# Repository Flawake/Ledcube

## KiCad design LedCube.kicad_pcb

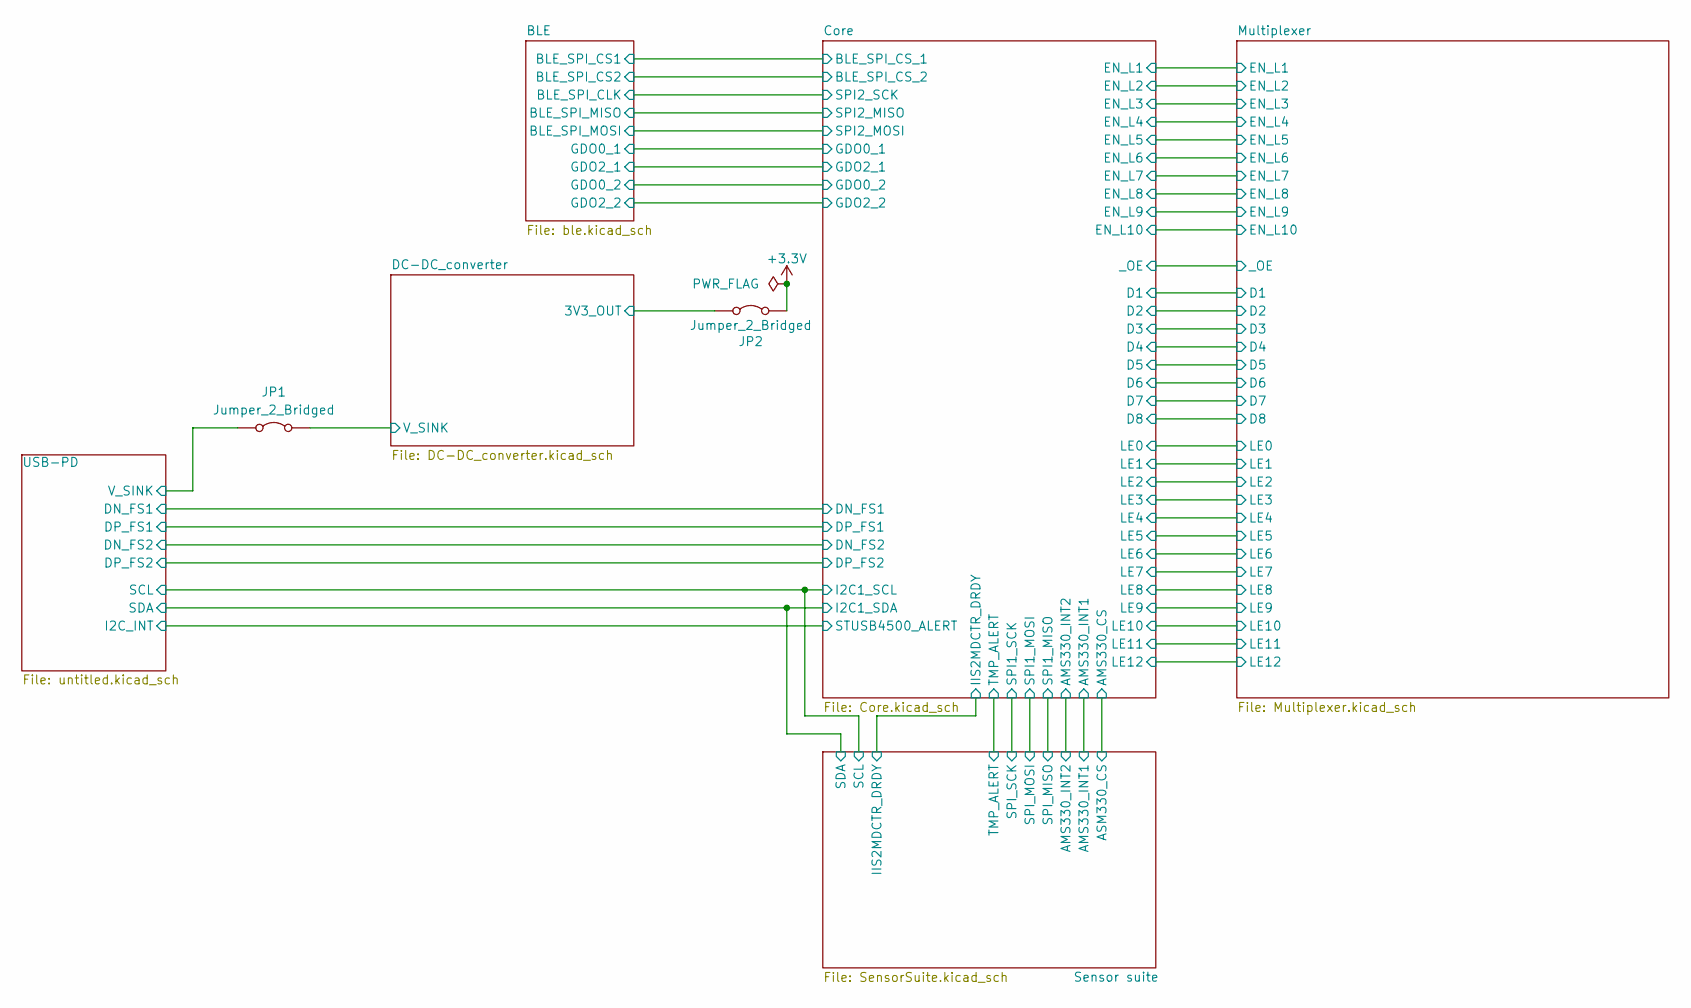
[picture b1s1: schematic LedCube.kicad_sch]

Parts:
JP1, JP2: Jumper_2_Bridged; R_0805_2012Metric

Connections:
+3.3V: JP2.2 (B); also elsewhere on the board
/DC-DC_converter/3V3_OUT: JP2.1 (A); also elsewhere on the board
/DC-DC_converter/V_SINK: JP1.2 (B); also elsewhere on the board
/USB-PD/V_SINK: JP1.1 (A); also elsewhere on the board

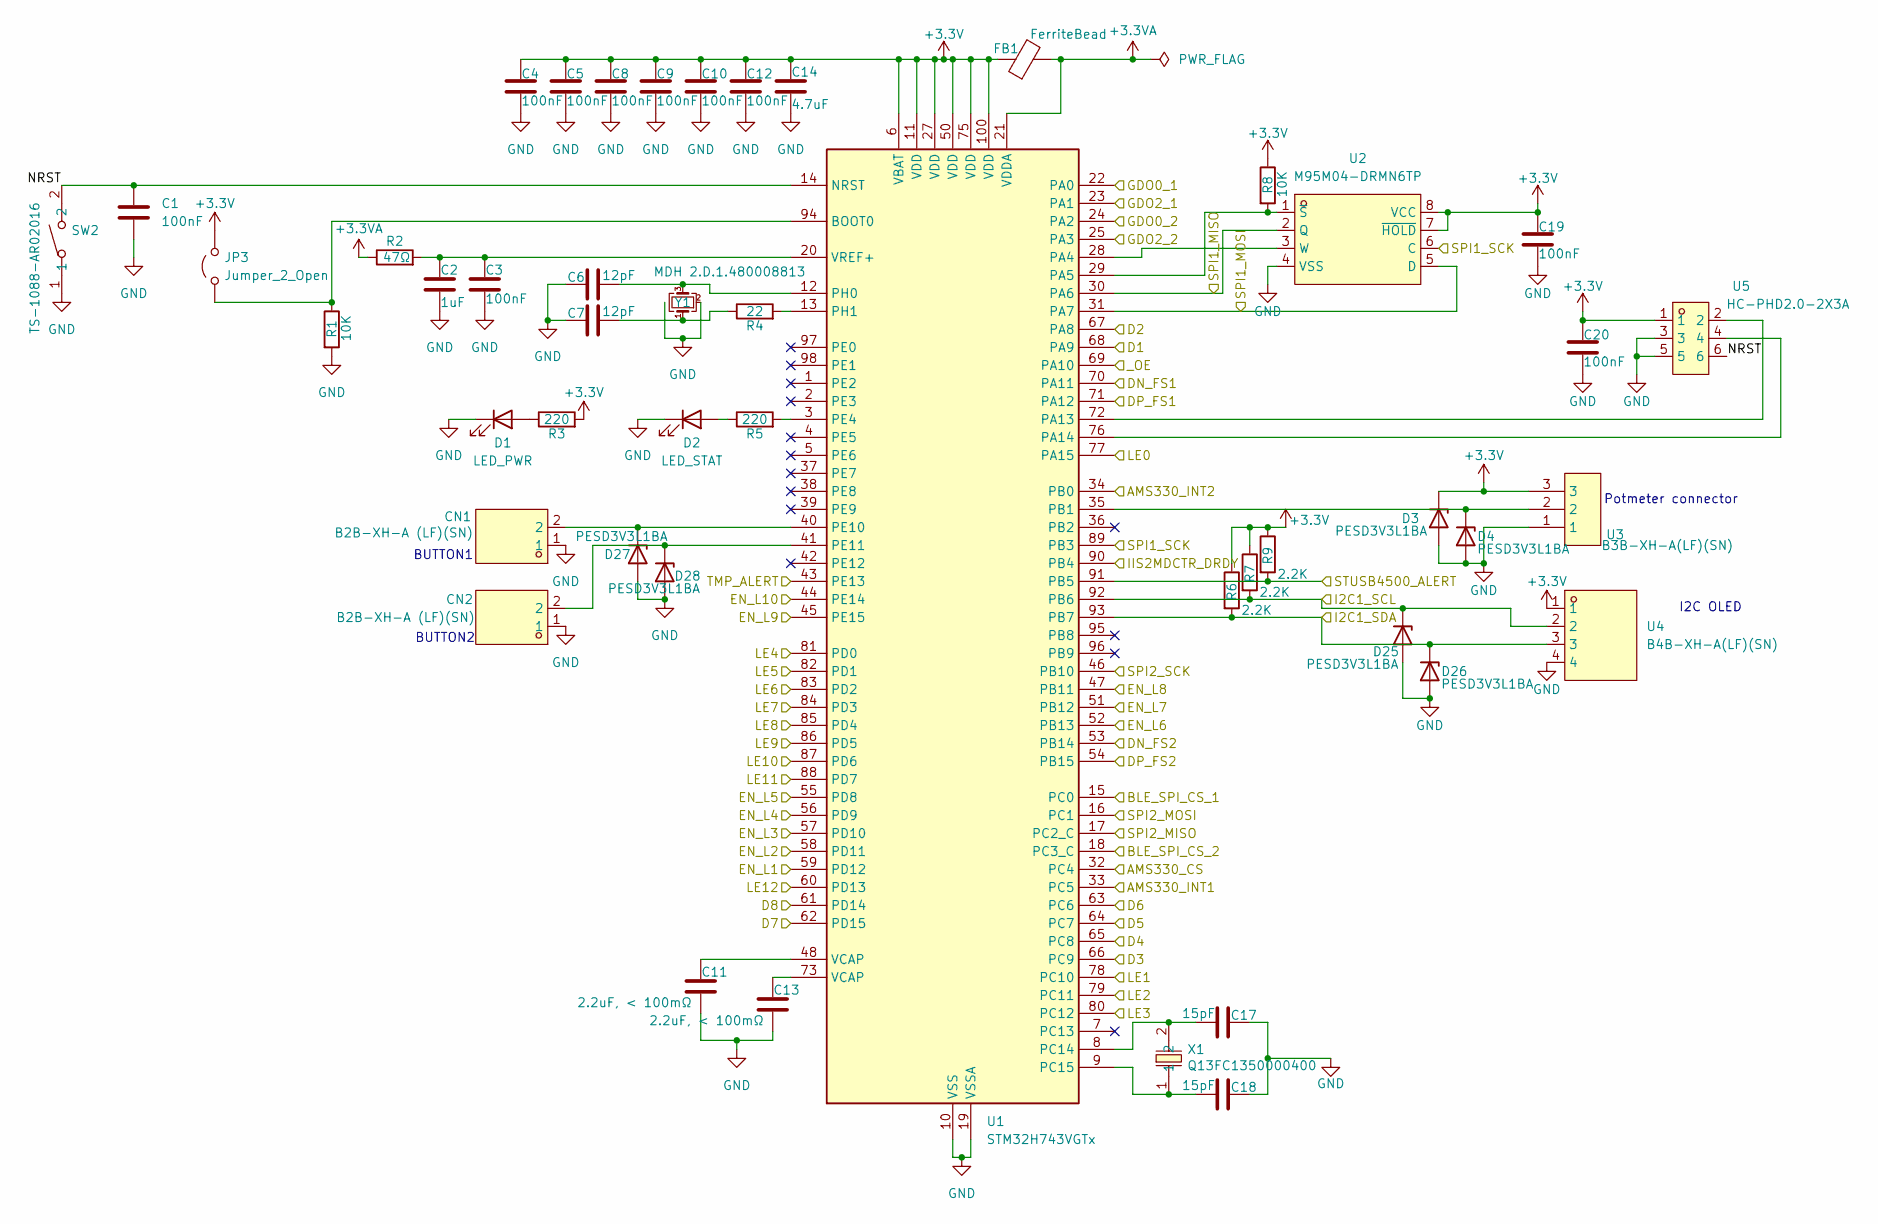
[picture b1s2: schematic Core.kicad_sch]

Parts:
C1, C3, C4, C5, C8, C9, C10, C12, C19, C20: 100nF; C_0603_1608Metric; LCSC C282519
C2: 1uF; C_0603_1608Metric; LCSC C29936
C6, C7: 12pF; C_0402_1005Metric; LCSC C76948
C11, C13: 2.2uF, < 100mΩ; C_0805_2012Metric; LCSC C19110
C14: 4.7uF; C_0603_1608Metric; LCSC C69335
C17, C18: 15pF; C_0402_1005Metric; LCSC C106997
CN1, CN2: B2B-XH-A (LF)(SN); CONN-TH_B2B-XH-A-LF-SN; LCSC Part C158012
D1: LED_PWR; LED_0603_1608Metric; LCSC C965804
D2: LED_STAT; LED_0603_1608Metric; LCSC C965799
D3, D4, D25, D26, D27, D28: PESD3V3L1BA; D_SOD-882; LCSC C22466620
FB1: FerriteBead; R_0402_1005Metric; Part muRata BLM18PG121SN1D; LCSC C76883
JP3: Jumper_2_Open; PinHeader_1x02_P2.54mm_Vertical
R1, R8: 10K; R_0603_1608Metric; LCSC C25804
R2: 47Ω; R_0603_1608Metric; LCSC C23182
R3, R5: 220; R_0603_1608Metric; LCSC C22962
R4: 22; R_0402_1005Metric; LCSC C2906914
R6, R7, R9: 2.2K; R_0402_1005Metric; LCSC C2906914
SW2: TS-1088-AR02016; SW-SMD_L3.9-W3.0-P4.45; LCSC Part C720477
U1: STM32H743VGTx; LQFP-100_14x14mm_P0.5mm
U2: M95M04-DRMN6TP; SOIC-8_L4.9-W3.9-P1.27-LS6.0-BL; LCSC Part C1852765
U3: B3B-XH-A(LF)(SN); CONN-TH_3P-P2.50_A2501WV2-3P; LCSC Part C144394
U4: B4B-XH-A(LF)(SN); CONN-TH_B4B-XH-A-LF-SN; LCSC Part C144395
U5: HC-PHD2.0-2X3A; HDR-TH_6P-P2.00-V-F-R2-C3-S2.00-4; LCSC Part C19273845
X1: Q13FC1350000400; FC-135R_L3.2-W1.5; LCSC Part C32346
Y1: MDH 2.D.1.480008813; Crystal_SMD_2016-4Pin_2.0x1.6mm; LCSC C42420969

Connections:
+3.3V: C4.1, C5.1, C8.1, C9.1, C10.1, C12.1, C14.1, C19.1, C20.1, D3.1 (K), FB1.1, JP3.2 (B), R3.2, R6.1, R7.1, R8.1, R9.1, U1.6 (VBAT), U1.11 (VDD), U1.27 (VDD), U1.50 (VDD), U1.75 (VDD), U1.100 (VDD), U2.7 (~HOLD), U2.8 (VCC), U3.3, U4.1, U5.1; also elsewhere on the board
+3.3VA: FB1.2, R2.1, U1.21 (VDDA)
/Core/AMS330_CS: U1.32 (PC4); also elsewhere on the board
/Core/AMS330_INT1: U1.33 (PC5); also elsewhere on the board
/Core/AMS330_INT2: U1.34 (PB0); also elsewhere on the board
/Core/BLE_SPI_CS_1: U1.15 (PC0)
/Core/BLE_SPI_CS_2: U1.18 (PC3_C)
/Core/D1: U1.68 (PA9); also elsewhere on the board
/Core/D2: U1.67 (PA8); also elsewhere on the board
/Core/D3: U1.66 (PC9); also elsewhere on the board
/Core/D4: U1.65 (PC8); also elsewhere on the board
/Core/D5: U1.64 (PC7); also elsewhere on the board
/Core/D6: U1.63 (PC6); also elsewhere on the board
/Core/D7: U1.62 (PD15); also elsewhere on the board
/Core/D8: U1.61 (PD14); also elsewhere on the board
/Core/EN_L1: U1.59 (PD12); also elsewhere on the board
/Core/EN_L2: U1.58 (PD11); also elsewhere on the board
/Core/EN_L3: U1.57 (PD10); also elsewhere on the board
/Core/EN_L4: U1.56 (PD9); also elsewhere on the board
/Core/EN_L5: U1.55 (PD8); also elsewhere on the board
/Core/EN_L6: U1.52 (PB13); also elsewhere on the board
/Core/EN_L7: U1.51 (PB12); also elsewhere on the board
/Core/EN_L8: U1.47 (PB11); also elsewhere on the board
/Core/EN_L9: U1.45 (PE15); also elsewhere on the board
/Core/EN_L10: U1.44 (PE14); also elsewhere on the board
/Core/GDO0_1: U1.22 (PA0)
/Core/GDO0_2: U1.24 (PA2)
/Core/GDO2_1: U1.23 (PA1)
/Core/GDO2_2: U1.25 (PA3)
/Core/I2C1_SCL: D25.1 (K), R7.2, U1.92 (PB6), U4.2; also elsewhere on the board
/Core/I2C1_SDA: D26.1 (K), R6.2, U1.93 (PB7), U4.3; also elsewhere on the board
/Core/IIS2MDCTR_DRDY: U1.90 (PB4); also elsewhere on the board
/Core/LE0: U1.77 (PA15); also elsewhere on the board
/Core/LE1: U1.78 (PC10); also elsewhere on the board
/Core/LE2: U1.79 (PC11); also elsewhere on the board
/Core/LE3: U1.80 (PC12); also elsewhere on the board
/Core/LE4: U1.81 (PD0); also elsewhere on the board
/Core/LE5: U1.82 (PD1); also elsewhere on the board
/Core/LE6: U1.83 (PD2); also elsewhere on the board
/Core/LE7: U1.84 (PD3); also elsewhere on the board
/Core/LE8: U1.85 (PD4); also elsewhere on the board
/Core/LE9: U1.86 (PD5); also elsewhere on the board
/Core/LE10: U1.87 (PD6); also elsewhere on the board
/Core/LE11: U1.88 (PD7); also elsewhere on the board
/Core/LE12: U1.60 (PD13); also elsewhere on the board
/Core/NRST: C1.1, SW2.2, U1.14 (NRST), U5.6
/Core/SPI1_MISO: U1.30 (PA6), U2.2 (Q); also elsewhere on the board
/Core/SPI1_MOSI: U1.31 (PA7), U2.5 (D); also elsewhere on the board
/Core/SPI1_SCK: U1.89 (PB3), U2.6 (C); also elsewhere on the board
/Core/SPI2_MISO: U1.17 (PC2_C)
/Core/SPI2_MOSI: U1.16 (PC1)
/Core/SPI2_SCK: U1.46 (PB10)
/Core/STUSB4500_ALERT: R9.2, U1.91 (PB5); also elsewhere on the board
/Core/TMP_ALERT: U1.43 (PE13); also elsewhere on the board
/Core/_OE: U1.69 (PA10); also elsewhere on the board
/USB-PD/D0+: U1.71 (PA12); also elsewhere on the board
/USB-PD/D0-: U1.70 (PA11); also elsewhere on the board
/USB-PD/D1+: U1.54 (PB15); also elsewhere on the board
/USB-PD/D1-: U1.53 (PB14); also elsewhere on the board
GND: C1.2, C2.2, C3.2, C4.2, C5.2, C6.1, C7.1, C8.2, C9.2, C10.2, C11.2, C12.2, C13.2, C14.2, C17.1, C18.1, C19.2, C20.2, CN1.1, CN2.1, D1.1 (K), D2.1 (K), D3.2 (A), D4.2 (A), D25.2 (A), D26.2 (A), D27.2 (A), D28.2 (A), R1.2, SW2.1, U1.10 (VSS), U1.19 (VSSA), U1.26 (VSS), U1.49 (VSS), U1.74 (VSS), U1.99 (VSS), U2.4 (VSS), U3.1, U4.4, U5.3, U5.5, Y1.2 (G), Y1.4 (G); also elsewhere on the board
unnamed: C7.2, R4.1, Y1.1
unnamed: C11.1, U1.48 (VCAP)
unnamed: C13.1, U1.73 (VCAP)
unnamed: D1.2 (A), R3.1
unnamed: D2.2 (A), R5.1
unnamed: D4.1 (K), U1.35 (PB1), U3.2
unnamed: CN1.2, D27.1 (K), U1.40 (PE10)
unnamed: CN2.2, D28.1 (K), U1.41 (PE11)
unnamed: JP3.1 (A), R1.1, U1.94 (BOOT0)
unnamed: U1.28 (PA4), U2.3 (W)
unnamed: R8.2, U1.29 (PA5), U2.1 (~S)
unnamed: U1.72 (PA13), U5.2
unnamed: U1.76 (PA14), U5.4
unnamed: C17.2, U1.8 (PC14), X1.2
unnamed: C18.2, U1.9 (PC15), X1.1
unnamed: R5.2, U1.3 (PE4)
unnamed: C6.2, U1.12 (PH0), Y1.3
unnamed: R4.2, U1.13 (PH1)
unnamed: C2.1, C3.1, R2.2, U1.20 (VREF+)

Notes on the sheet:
BUTTON2
BUTTON1
I2C OLED
Potmeter connector

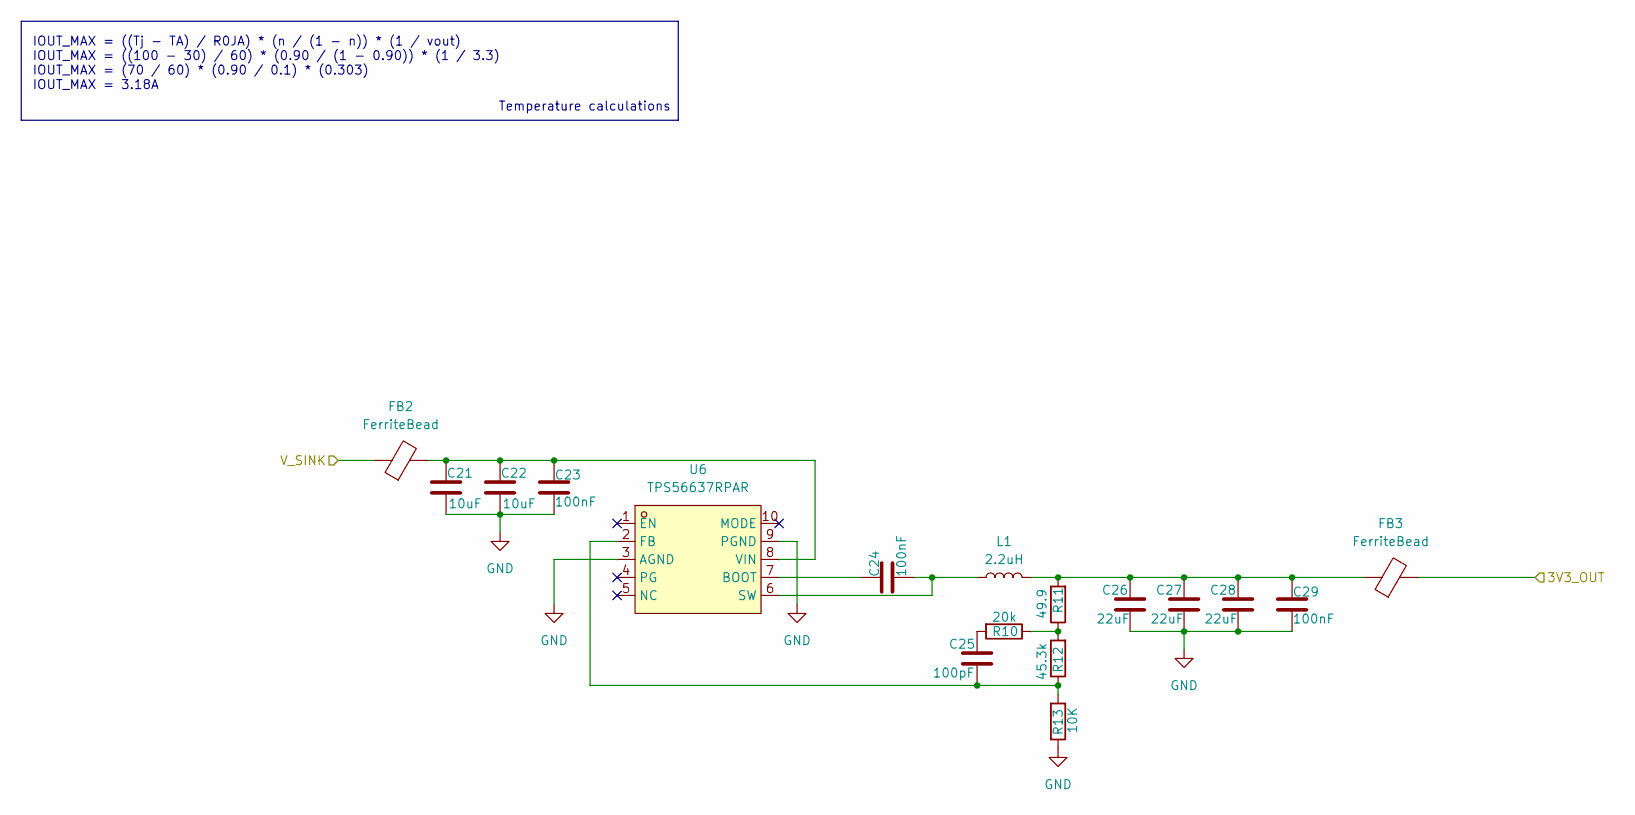
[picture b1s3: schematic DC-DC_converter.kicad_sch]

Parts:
C21, C22: 10uF; C_0805_2012Metric; LCSC C440198
C23, C24, C29: 100nF; C_0603_1608Metric; LCSC C282519
C25: 100pF; C_0402_1005Metric; LCSC C26409
C26, C27, C28: 22uF; C_0603_1608Metric; LCSC C86295
FB2, FB3: FerriteBead; R_0805_2012Metric; LCSC C16903
L1: 2.2uH; L_Chilisin_BMRB00050518-B; LCSC C5349681
R10: 20k; R_0402_1005Metric; LCSC C2906914
R11: 49.9; R_0603_1608Metric; LCSC C2907011
R12: 45.3k; R_0603_1608Metric; LCSC C23058
R13: 10K; R_0603_1608Metric; LCSC C25804
U6: TPS56637RPAR; VQFN-HR-10_L3.0-W3.0_RPA; LCSC Part C841386

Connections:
/DC-DC_converter/3V3_OUT: FB3.2; also elsewhere on the board
/DC-DC_converter/V_SINK: FB2.1; also elsewhere on the board
GND: C21.2, C22.2, C23.2, C26.2, C27.2, C28.2, C29.2, R13.2, U6.3 (AGND), U6.9 (PGND); also elsewhere on the board
unnamed: C25.1, R10.2
unnamed: C26.1, C27.1, C28.1, C29.1, FB3.1, L1.2, R11.2
unnamed: R10.1, R11.1, R12.2
unnamed: C24.1, U6.7 (BOOT)
unnamed: C25.2, R12.1, R13.1, U6.2 (FB)
unnamed: C24.2, L1.1, U6.6 (SW)
unnamed: C21.1, C22.1, C23.1, FB2.2, U6.8 (VIN)

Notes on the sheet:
Temperature calculations
IOUT_MAX = ((Tj - TA) / R0JA) * (n / (1 - n)) * (1 / vout) IOUT_MAX = ((100 - 30) / 60) * (0.90 / (1 - 0.90)) * (1 / 3.3) IOUT_MAX = (70 / 60) * (0.90 / 0.1) * (0.303) IOUT_MAX = 3.18A

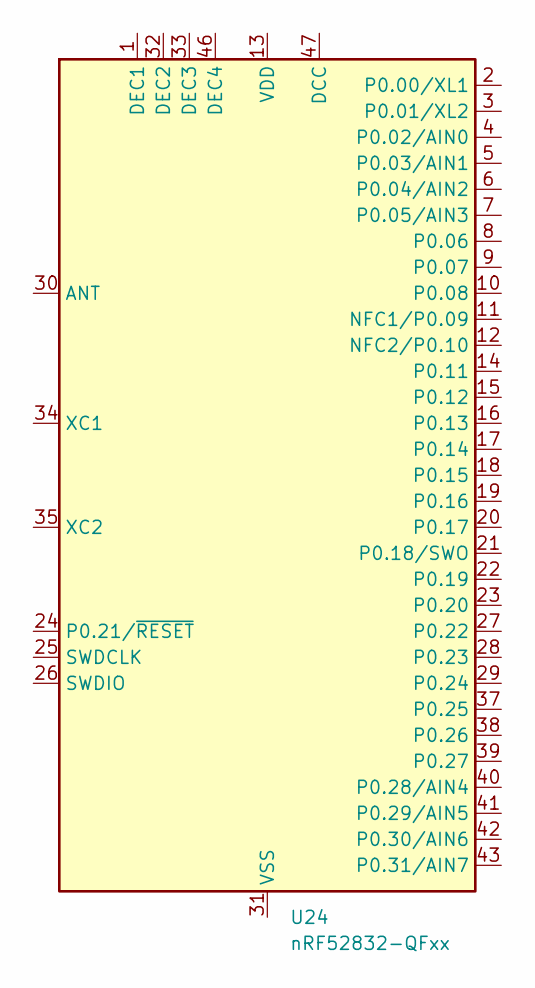
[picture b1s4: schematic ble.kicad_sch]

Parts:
U24: nRF52832-QFxx; QFN-48-1EP_6x6mm_P0.4mm_EP4.6x4.6mm

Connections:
unnamed: U24.13 (VDD), U24.36 (VDD), U24.48 (VDD)
unnamed: U24.31 (VSS), U24.45 (VSS), U24.49 (VSS)

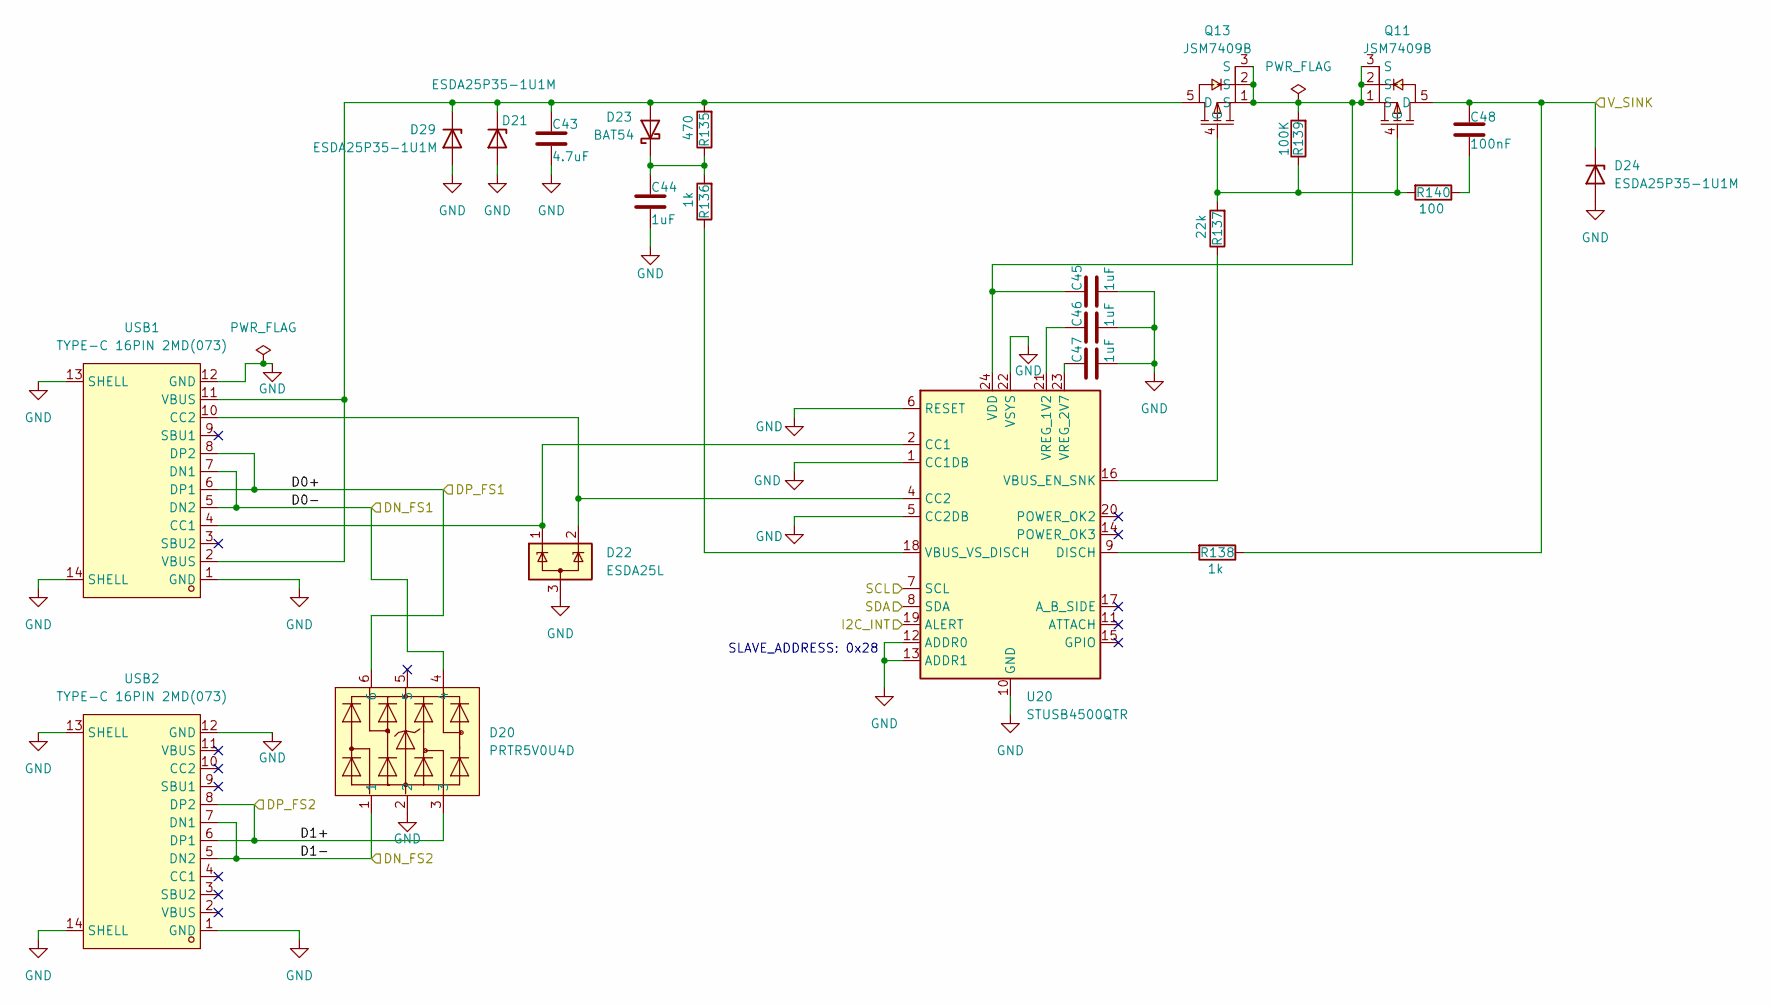
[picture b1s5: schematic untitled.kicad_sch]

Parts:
C43: 4.7uF; C_0603_1608Metric; LCSC C69335
C44, C45, C46, C47: 1uF; C_0603_1608Metric; LCSC C29936
C48: 100nF; C_0603_1608Metric; LCSC C282519
D20: PRTR5V0U4D; SOT-23-6_L2.9-W1.6-P0.95-LS2.8-BR; LCSC Part C29779750
D21, D24, D29: ESDA25P35-1U1M; D_SOD-882; LCSC C19170853
D22: ESDA25L; SOT-23-3
D23: BAT54; TSOT-23; LCSC C408389
Q11, Q13: JSM7409B; POWERVDFN-8_L3.2-W3.1-P0.65-LS3.3-BL-1; LCSC Part C2874718
R135: 470; R_1206_3216Metric; LCSC C2930375
R136, R138: 1k; R_0603_1608Metric; LCSC C22548
R137: 22k; R_0603_1608Metric; LCSC C2907128
R139: 100K; R_0603_1608Metric; LCSC C25803
R140: 100; R_0603_1608Metric; LCSC C2907089
U20: STUSB4500QTR; QFN-24-1EP_4x4mm_P0.5mm_EP2.7x2.7mm
USB1, USB2: TYPE-C 16PIN 2MD(073); USB-C-SMD_TYPE-C-6PIN-2MD-073; LCSC Part C2765186

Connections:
/Core/I2C1_SCL: U20.7 (SCL); also elsewhere on the board
/Core/I2C1_SDA: U20.8 (SDA); also elsewhere on the board
/Core/STUSB4500_ALERT: U20.19 (ALERT); also elsewhere on the board
/USB-PD/D0+: D20.6, USB1.6 (DP1), USB1.8 (DP2); also elsewhere on the board
/USB-PD/D0-: D20.4, USB1.5 (DN2), USB1.7 (DN1); also elsewhere on the board
/USB-PD/D1+: D20.3, USB2.6 (DP1), USB2.8 (DP2); also elsewhere on the board
/USB-PD/D1-: D20.1, USB2.5 (DN2), USB2.7 (DN1); also elsewhere on the board
/USB-PD/V_SINK: C48.1, D24.1 (K), Q11.5 (D), R138.1; also elsewhere on the board
GND: C43.2, C44.2, C45.2, C46.2, C47.2, D20.2, D21.2 (A), D22.3 (A), D24.2 (A), D29.2 (A), U20.1 (CC1DB), U20.5 (CC2DB), U20.6 (RESET), U20.10 (GND), U20.12 (ADDR0), U20.13 (ADDR1), U20.22 (VSYS), U20.25 (GND), USB1.1 (GND), USB1.12 (GND), USB1.13 (SHELL), USB1.14 (SHELL), USB2.1 (GND), USB2.12 (GND), USB2.13 (SHELL), USB2.14 (SHELL); also elsewhere on the board
unnamed: C48.2, R140.1
unnamed: C43.1, D21.1 (K), D23.2 (A), D29.1 (K), Q13.5 (D), R135.2, USB1.2 (VBUS), USB1.11 (VBUS)
unnamed: C44.1, D23.1 (K), R135.1, R136.2
unnamed: Q11.4 (G), Q13.4 (G), R137.2, R139.1, R140.2
unnamed: D22.1 (K), U20.2 (CC1), USB1.4 (CC1)
unnamed: D22.2 (K), U20.4 (CC2), USB1.10 (CC2)
unnamed: R138.2, U20.9 (DISCH)
unnamed: R137.1, U20.16 (VBUS_EN_SNK)
unnamed: R136.1, U20.18 (VBUS_VS_DISCH)
unnamed: C45.1, Q11.1 (S), Q11.2 (S), Q11.3 (S), Q13.1 (S), Q13.2 (S), Q13.3 (S), R139.2, U20.24 (VDD)
unnamed: C46.1, U20.21 (VREG_1V2)
unnamed: C47.1, U20.23 (VREG_2V7)

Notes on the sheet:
SLAVE_ADDRESS: 0x28
